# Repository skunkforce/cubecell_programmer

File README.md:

# cubecell_programmer
DEPRICATED! see c004_ESP32_S3_usb_debugger in this organisation
## octopart BOM
https://octopart.com/bom-tool/e3DcL6kq/l8JbL5GodMYzifxL

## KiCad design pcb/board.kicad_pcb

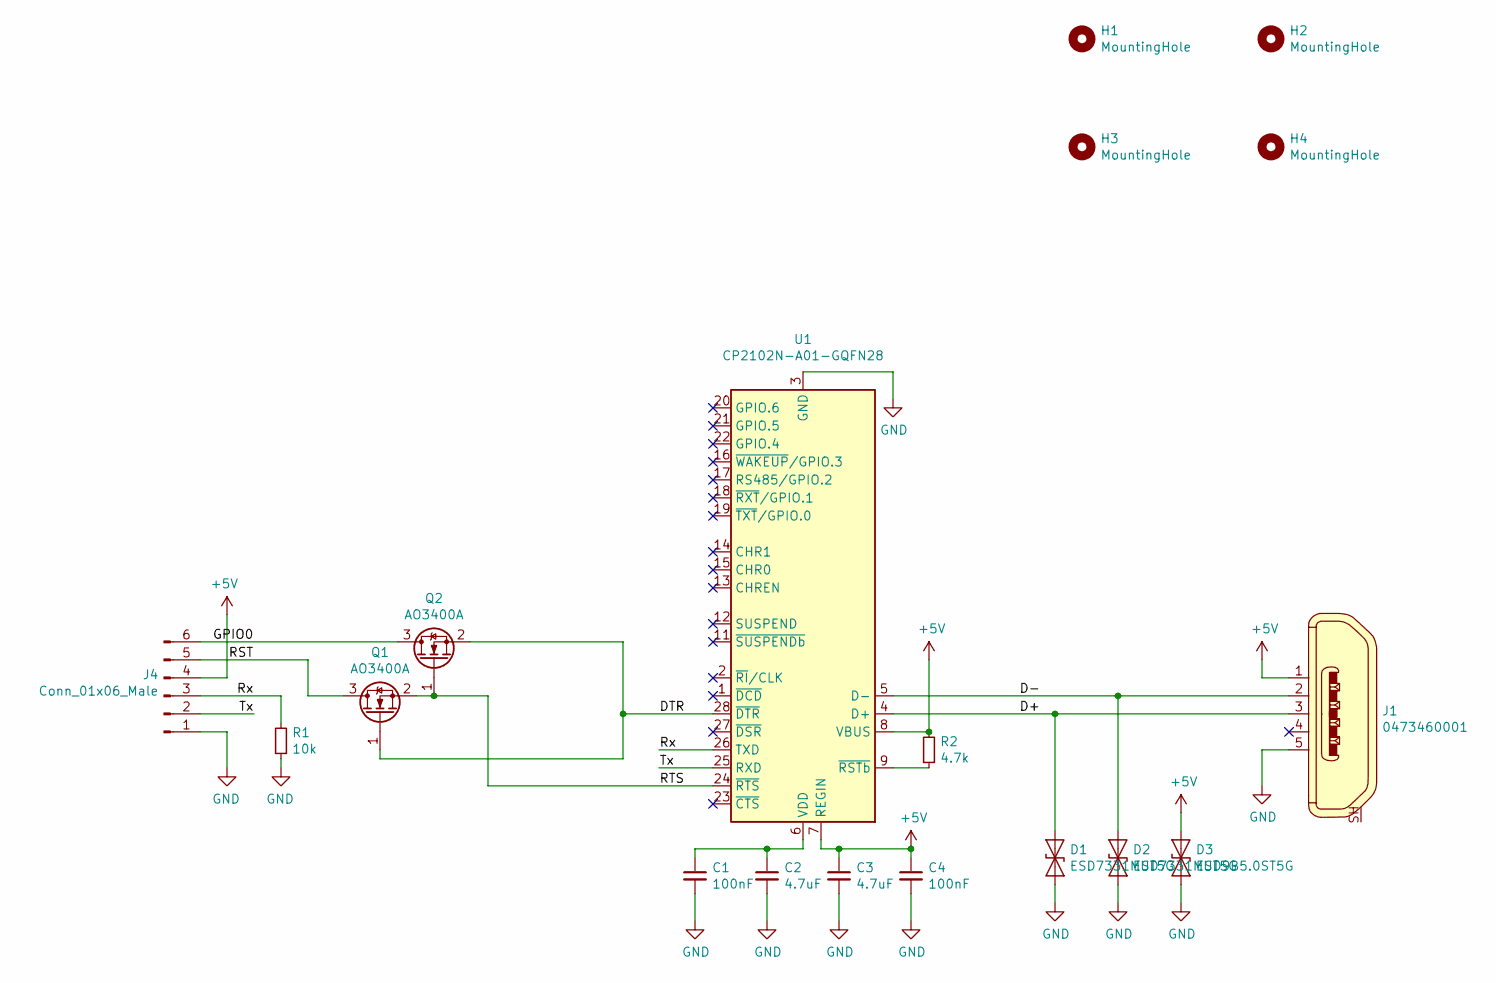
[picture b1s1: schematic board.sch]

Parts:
C1, C4: 100nF; C_0603_1608Metric
C2, C3: 4.7uF; C_0603_1608Metric
D1, D2: ESD7331MUT5G; D_0201_0603Metric
D3: ESD9B5.0ST5G; D_0402_1005Metric
H1, H2, H3, H4: MountingHole; MountingHole_3.2mm_M3; MPN N/P; Digi-Key_PN N/P
J1: 0473460001; USB_Micro_B_Female_0473460001; MPN 0473460001; Digi-Key_PN WM17141CT-ND
J4: Conn_01x06_Male; PinHeader_1x06_P2.54mm_Vertical
Q1, Q2: AO3400A; SOT-23; MPN AO3400A; Digi-Key_PN 785-1000-1-ND
R1: 10k; R_0603_1608Metric
R2: 4.7k; R_0603_1608Metric
U1: CP2102N-A01-GQFN28; QFN-28-1EP_5x5mm_P0.5mm_EP3.35x3.35mm

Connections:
+5V: C3.1, C4.1, D3.1 (A1), J1.1, J4.4, R2.2, U1.7 (REGIN), U1.8 (VBUS)
/D+: D1.1 (A1), J1.3, U1.4 (D+)
/D-: D2.1 (A1), J1.2, U1.5 (D-)
/DTR: Q1.1 (G), Q2.2 (S), U1.28 (~DTR)
/GPIO0: J4.6, Q2.3 (D)
/RST: J4.5, Q1.3 (D)
/RTS: Q1.2 (S), Q2.1 (G), U1.24 (~RTS)
/Rx: J4.3, R1.2, U1.26 (TXD)
/Tx: J4.2, U1.25 (RXD)
GND: C1.2, C2.2, C3.2, C4.2, D1.2 (A2), D2.2 (A2), D3.2 (A2), J1.5, J4.1, R1.1, U1.3 (GND), U1.29 (GND)
unnamed: C1.1, C2.1, U1.6 (VDD)
unnamed: R2.1, U1.9 (~RSTb)

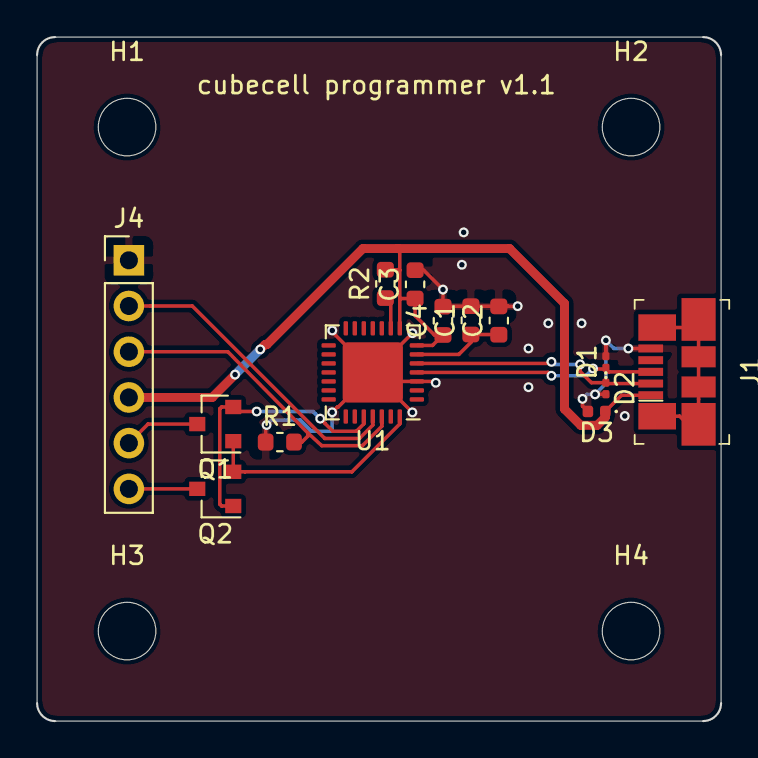
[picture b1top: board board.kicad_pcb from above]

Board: 2 copper layers, 38.0 x 38.0 mm, 18 parts (0 on the bottom side), 12 nets.

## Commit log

2020-05-17 initial
2020-05-18 fixed missing 5v connection and changed ESD diodes
2020-05-22 octopart bom
